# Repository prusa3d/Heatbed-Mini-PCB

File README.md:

# PRUSA 7' Heatbed for Mini

KiCad PCB layout

* [Interactive bom](http://htmlpreview.github.io/?https://github.com/prusa3d/Heatbed-Mini-PCB/blob/master/rev.03b/ibom.html)
* [STEP 3D model](rev.03b/Heatbed-007-03b.step)

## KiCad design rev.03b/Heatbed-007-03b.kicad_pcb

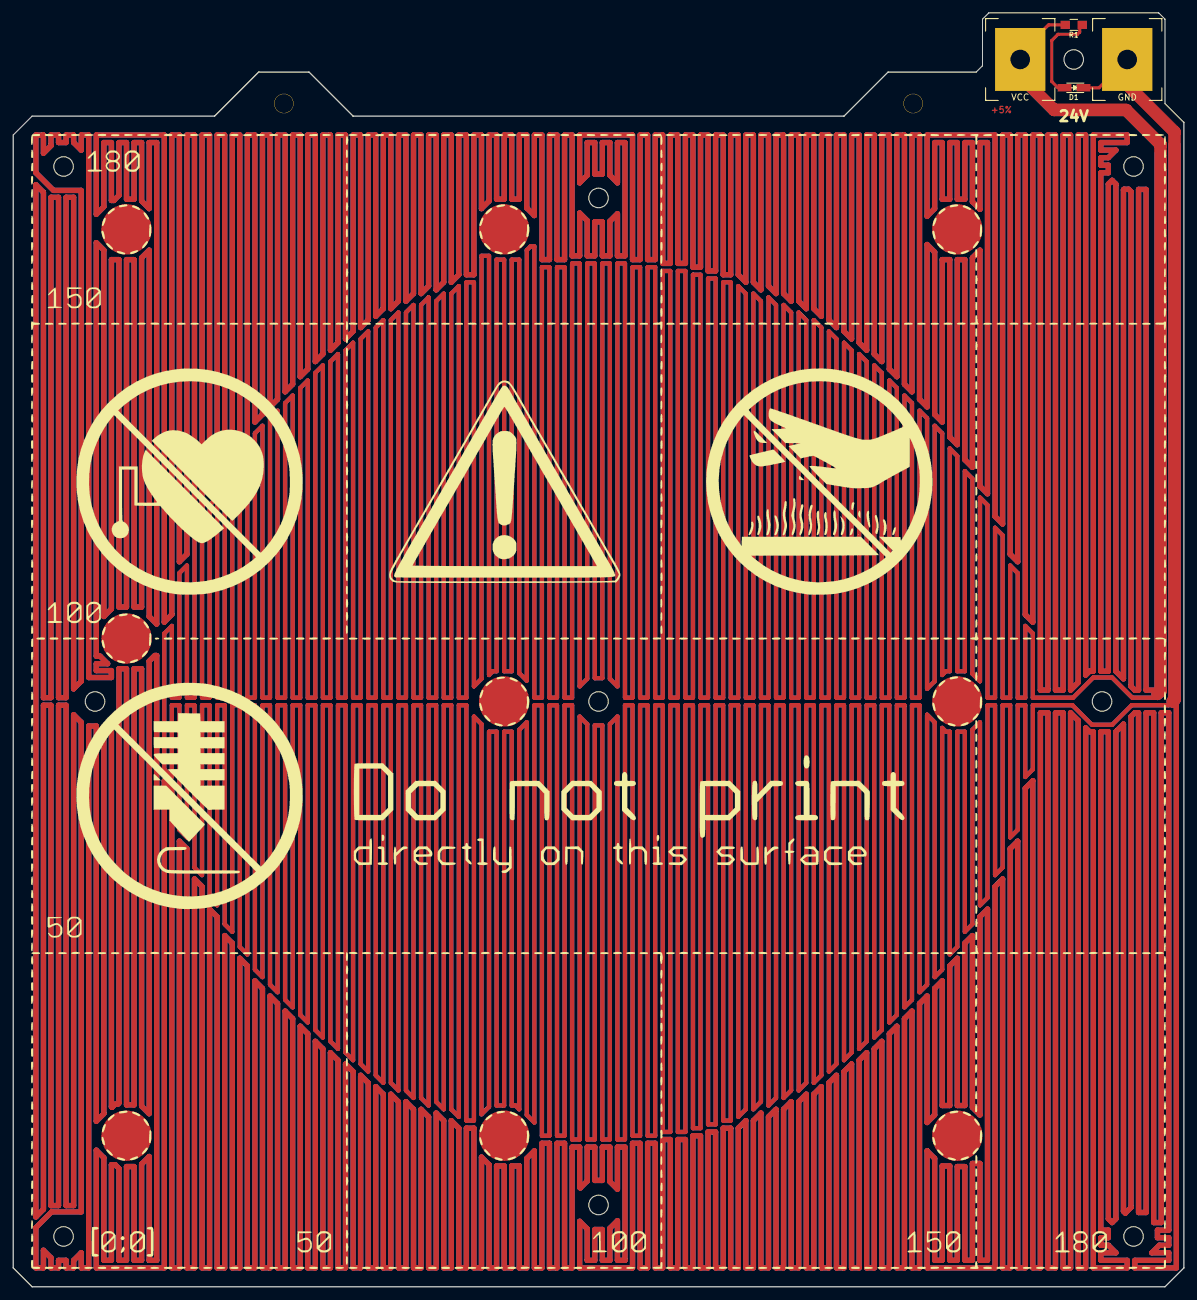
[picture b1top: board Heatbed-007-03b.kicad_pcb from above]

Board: 2 copper layers, 186.0 x 202.4 mm, 4 parts (0 on the bottom side), 2 nets.

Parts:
D1: LTST-C170CKT; LED_0805
P1: VCC; PCB-Large-pad
P2: GND; PCB-Large-pad
R1: 2k2; R_0805_HandSoldering

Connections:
unnamed: D1.1, P1.1, P2.1, R1.1
unnamed: D1.2, R1.2

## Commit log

2019-12-10 fix url
